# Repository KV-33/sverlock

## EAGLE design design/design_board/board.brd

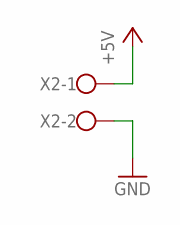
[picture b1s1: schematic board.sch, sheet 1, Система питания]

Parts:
X2: W237-102

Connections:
+5V: X2.1; also elsewhere on the board
GND: X2.2; also elsewhere on the board

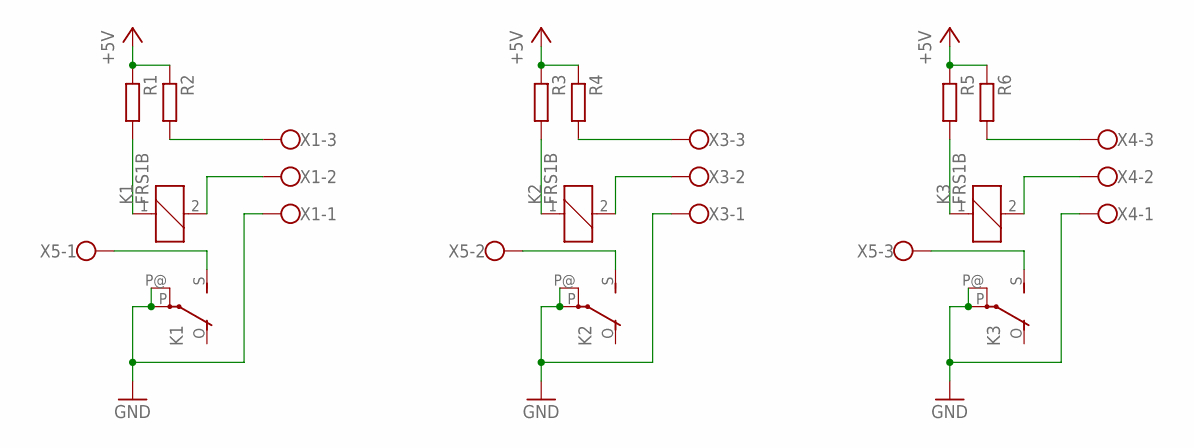
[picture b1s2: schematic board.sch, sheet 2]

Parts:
K1, K2, K3: FRS1B
R1, R2, R3, R4, R5, R6: R-EU_0207/12; 0207/12
X1, X3, X4, X5: W237-103

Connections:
+5V: R1.1, R2.1, R3.1, R4.1, R5.1, R6.1; also elsewhere on the board
GND: K1.P, K1.P@, K2.P, K2.P@, K3.P, K3.P@, X1.1, X3.1, X4.1; also elsewhere on the board
unnamed: K1.1, R1.2
unnamed: R2.2, X1.3
unnamed: K1.2, X1.2
unnamed: K1.S, X5.1
unnamed: K2.1, R3.2
unnamed: R4.2, X3.3
unnamed: K2.2, X3.2
unnamed: K2.S, X5.2
unnamed: K3.1, R5.2
unnamed: R6.2, X4.3
unnamed: K3.2, X4.2
unnamed: K3.S, X5.3

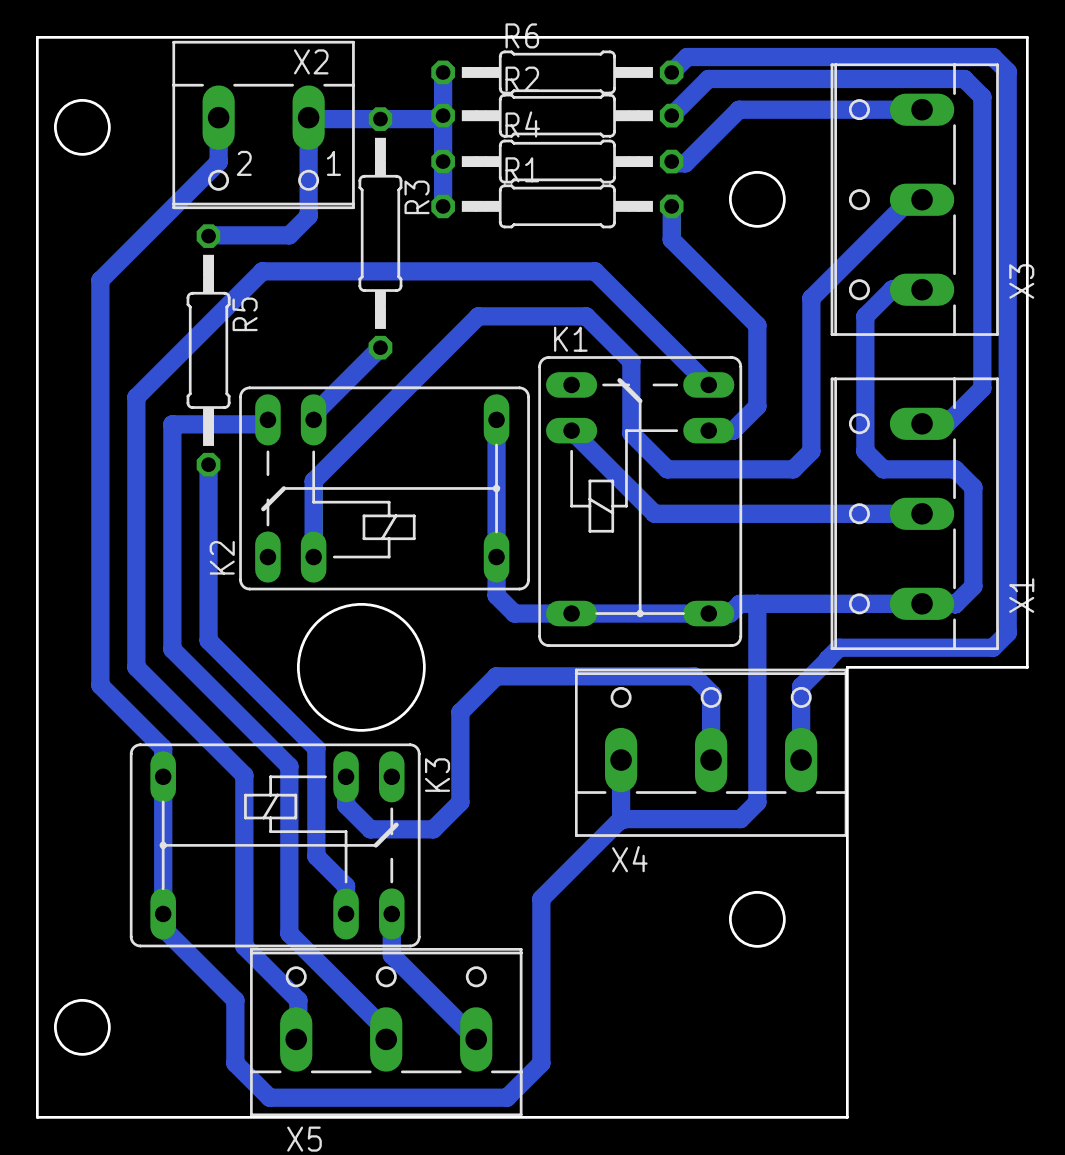
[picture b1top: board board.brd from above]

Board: 2 copper layers, 55.0 x 60.0 mm, 14 parts (0 on the bottom side), 14 nets.

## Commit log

2020-12-09 Добавлена плата переходник для датчиков
